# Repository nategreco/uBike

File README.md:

# Universal Bike Controller
The Universal Bike Controller is an open-source project aimed at providing a drop-in replacement for the factory console on NordicTrack® S-series exercise bikes (s10i, s15i, s22i, and s27i). This project allows you to upgrade and customize your bike's control system with new features and improvements.

## Explanation
The factory consoles on NordicTrack® S-series bikes may lack certain features or customization options that users desire. The Universal Bike Controller project addresses these limitations by providing an open-source solution that simplifies the hardware on the bike while unlocking connectivity to other third-party apps (Zwift®, Rouvy®, Peloton®) and smart devices.

(Tablet not included)

## Features
- Drop-in replacement controller for the iFit console
  - **Note - This controller and the OEM console cannot be used together**
- Full incline and resistance control via OEM handlebar pushbuttons
- Wireless connectivity to a variety of third-party applications
- 3.5" TFT touchscreen for reseting elapsed time
- USB Type A fast charger port for charging
- Over-the-air support for future software upgrades

## Installation
The replacement uBike console mounts in the current location of the weight tray and plugs into the same two cables as the factory console. Installation is as simple as follows:
1. Turn off the bike
1. Remove the 4 screws from the underside of the weight tray (save them) and remove the weight tray
1. Place the uBike controller in its place, with the connectors facing away from the rider
1. Use the same 4 screws removed from the weight tray to secure the uBike controller
1. Unplug the 2 cables from the factory console and plug them into the new uBike controller
  * **Please see note below on compatability if you do not have a red and yellow connector**

## Compatibility
The Universal Bike Controller is designed to be compatible with the following NordicTrack® S-series exercise bikes:
- s10i
- s15i
- s22i
- s27i

All of these versions have been tested and are working.  Additionally, since 2021 bikes have stopped shipping with the yellow and red mini-DIN connectors to the console, instead they have cables coming directly out of the console.  **If your bike does not have the red and yellow connectors** you will need to buy the cables below:
* Yellow mini-DIN-6 Connector - PN 411540 ([eBay](https://www.ebay.com/itm/255061719835)/[HydraFitness](https://hydrafitnessparts.com/collections/stationary-bike-wires-and-wire-harness/products/nordictrack-comm-s22i-s15i-s10i-stationary-bike-upper-wire-harness-411540))
* Red mini-DIN-8 Connector - PN 411536 ([eBay](https://www.ebay.com/itm/265237954787)/[HydraFitness](https://hydrafitnessparts.com/collections/stationary-bike-wires-and-wire-harness/products/nordictrack-comm-s22i-s15i-s10i-stationary-bike-extension-wire-harness-411536))

## Additional Reference Photos

## Development
Contributing to the project is encouraged and can be done by testing and reporting issues or software/hardware development.

### Hardware Overview
The hardware is composed of the following components:
* Controller PCB board
* [4D LCD 3.5" Capacitive Touch TFT-LCD](https://4dsystems.com.au/products/4dlcd-35480320-ctp-clb-ips/) 
* Controller enclosure
* Base mount for the enclosure

### Software Tools
* FreeCAD - Housing modeling
* KiCad - PCB Design
* nRF Connect 2.3.0 w/ Visual Studio Code extension - Firmware Development
* Python - Misc development and testing scripts

### Building Firmware
* Open folder `firmware/zephyr-project` in VS Code
* Open nRF Connect extension and press 'Create Build Configuration'
* Select 'ubike_v03' board
* Use defaults and press 'Build Configuration'
* Should produce a binary in `firmware/zephyr-project/build/zephyr/zephyr.hex`

### Flashing
* Open nRF Connect Programmer
* Press 'Add file' and select `firmware/zephyr-project/build/zephyr/zephyr.hex`
* Connect a [nRF52840 DK development board](https://www.nordicsemi.com/Products/Development-hardware/nRF52840-DK) or other SWD/JTAG programmer
* Select the development board as programming device
* Press 'Erase & write'

## Authors
* [@nategreco](https://github.com/nategreco)

## Need Hardware?
[Check out our store on Tindie](https://www.tindie.com/products/grecoengineer/universal-bike-controller/)

**Disclaimer**: This project is not affiliated with or endorsed by ICON Health Fitness, Inc (Nordictrack®) or its parent company. Use this software at your own risk, and be aware that modifying your exercise bike may void any warranties.

---

Contributions, feedback, and bug reports are welcome. Feel free to fork, contribute, or open issues to improve the Universal Bike Controller project!

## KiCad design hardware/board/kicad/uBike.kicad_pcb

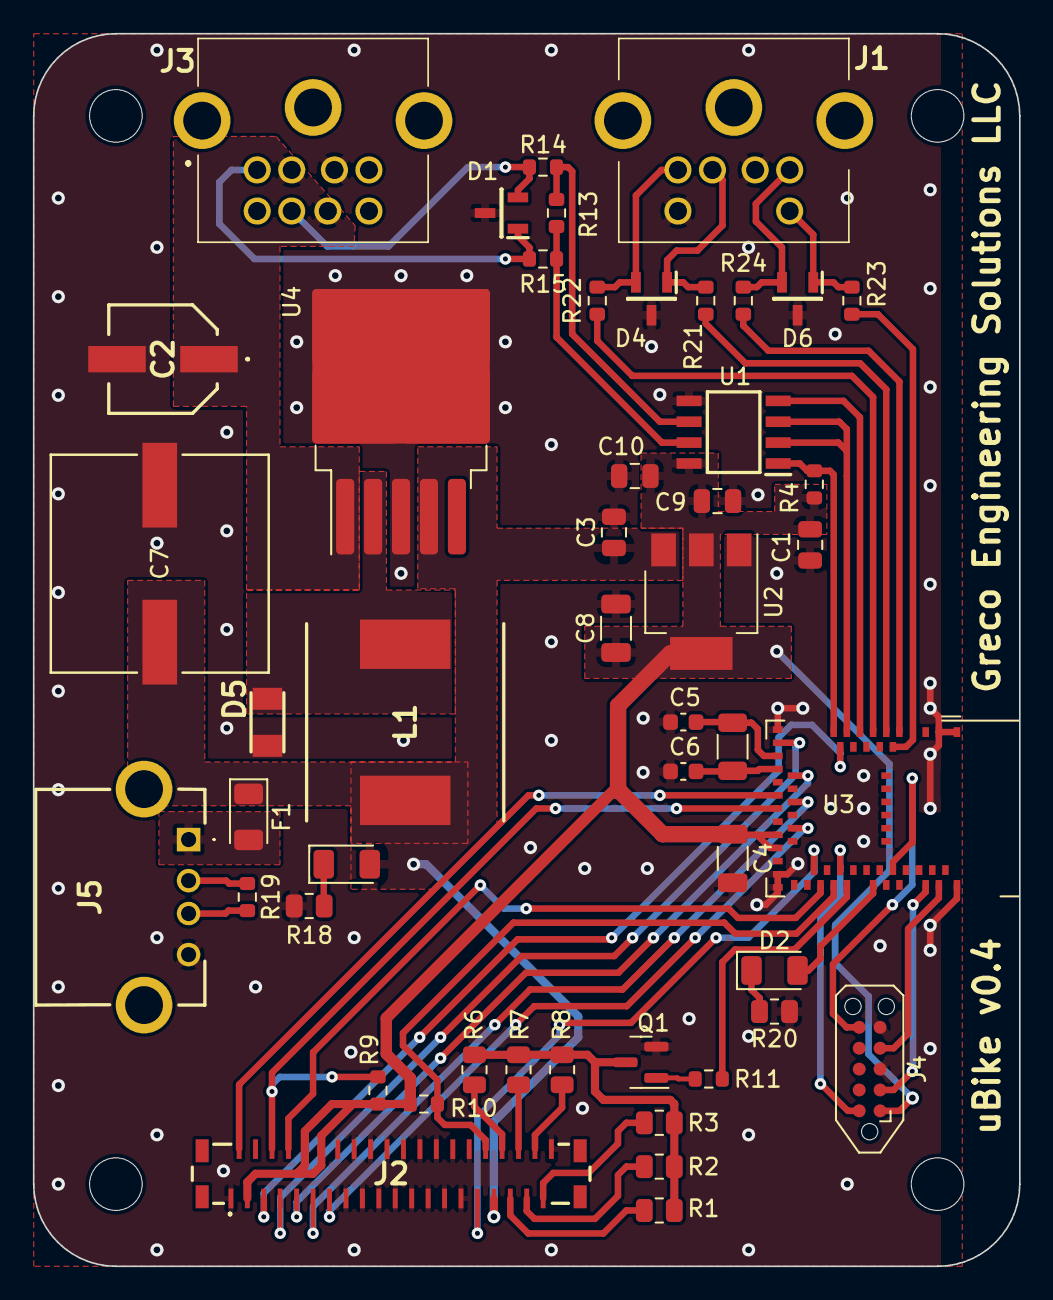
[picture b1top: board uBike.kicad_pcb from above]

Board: 2 copper layers, 60.0 x 75.0 mm, 53 parts (0 on the bottom side), 51 nets.

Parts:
C1, C3, C9: 100n; C_0805_2012Metric
C2: 120u; 16SVF180M
C4, C8: 10u; C_1206_3216Metric
C5, C6: 12p; C_0603_1608Metric
C7: 220u; CHEMI-KE0
C10: 1u; C_0805_2012Metric
D1, D4, D6: CDSOT23-SM712; SOT95P230X117-3N
D2: GREEN; D_1206_3216Metric
D3: RED; D_1206_3216Metric
D5: SS24FL; SODFL3617X108N
F1: 2A; D_1206_3216Metric
H1, H2, H3, H4: MountingHole; MountingHole_3.2mm_M3
J1: KMDGX-6S-BS; KMDGX6SBS
J2: F31S-1A7L1-11040; F31S1A7L111040
J3: KMDGX-8S-BS; KMDGX8SBS
J4: TC2050-IDC-NL; Tag-Connect_TC2050-IDC-NL_2x05_P1.27mm_Vertical
J5: 87520-0010BLF
L1: MSS1210-683MED; INDPM120120X1020N
Q1: MMBT3904; SOT-23
R1, R2, R3, R6, R7, R8, R20: 68; R_0805_2012Metric
R4: 10k; R_0603_1608Metric
R9, R10: 1k69; R_0603_1608Metric
R11: 1k; R_0603_1608Metric
R13: 250; R_0603_1608Metric
R14, R15, R21, R22, R23, R24: 10; R_0603_1608Metric
R18: 330; R_0805_2012Metric
R19: 150; R_0603_1608Metric
U1: SN65HVD08DR; SOIC127P600X175-8N
U2: LD1117S33TR_SOT223; SOT-223-3_TabPin2
U3: MDBT50Q-P1MV2; Raytac_MDBT50Q
U4: LM2596S-5; TO-263-5_TabPin3
X1: 32.768kHz; R_1206_3216Metric

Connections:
+3.3V: C1.1, C4.1, C8.1, C9.2, C10.2, J2.3, J2.10, J2.12, J4.1, R4.1, R9.1, R10.1, U1.8 (VCC), U2.2 (VO), U3.28 (VDD), U3.30 (VDDH)
+5V: C3.1, C7.1, D3.2 (A), F1.1, J2.33, L1.2, U2.3 (VI), U4.4 (FB)
+12V: C2.1 (+), J3.1, J3.7, U4.1 (VIN)
BL_DRAIN: Q1.3 (C), R1.1, R2.1, R3.1, R6.2, R7.2, R8.2
BL_PWM: R11.1, U3.41 (P0.17)
CS: J2.9, U3.19 (P0.26)
CTP_SCL: J2.6, R9.2, U3.24 (P0.08)
CTP_SDA: J2.32, R10.2, U3.39 (P0.15)
DE: U1.2 (~RE), U1.3 (DE), U3.12 (P0.31/AIN7)
GND: C1.2, C2.2 (-), C3.2, C4.2, C5.2, C6.2, C7.2, C8.2, C9.1, C10.1, D1.3, D4.3, D5.2 (A), D6.3, J1.2, J1.6, J2.1, J2.14, J2.15, J2.16, J2.17, J2.18, J2.19, J2.20, J2.21, J2.22, J2.23, J2.24, J2.25, J2.26, J2.27, J2.28, J2.29, J2.30, J2.40, J3.2, J3.6, J4.3, J4.5, J5.4, Q1.2 (E), R18.1, R20.1, U1.5 (GND), U2.1 (GND), U3.1 (GND), U3.2 (GND), U3.15 (GND), U3.32 (VBUS), U3.33 (GND), U3.55 (GND), U4.3 (GND)
IN1: R21.1, U3.6 (P1.13)
IN2: R22.2, U3.8 (P1.15)
IN3: R24.2, U3.4 (P1.11)
IN4: R23.1, U3.5 (P1.12)
unnamed: D2.2 (A), U3.44 (P0.20)
unnamed: D2.1 (K), R20.2
unnamed: D3.1 (K), R18.2
unnamed: D4.1, J1.1, R21.2
unnamed: D4.2, J1.3, R22.1
unnamed: D5.1 (K), L1.1, U4.2 (OUT)
unnamed: D6.1, J1.8, R23.2
unnamed: D6.2, J1.5, R24.1
unnamed: F1.2, J5.1
unnamed: J2.34, R6.1
unnamed: J2.35, R1.2
unnamed: J2.36, R7.1
unnamed: J2.37, R2.2
unnamed: J2.38, R8.1
unnamed: J2.39, R3.2
unnamed: J5.2, R19.1
unnamed: J5.3, R19.2
unnamed: Q1.1 (B), R11.2
unnamed: R13.2, R14.2, U1.6 (A)
unnamed: R13.1, R15.2, U1.7 (B)
unnamed: C5.1, U3.17 (XL1/P0.00), X1.2
unnamed: C6.1, U3.18 (XL2/P0.01), X1.1
RESET: J2.7, U3.16 (P0.27)
RS: J2.8, U3.37 (P0.13)
RS485_A: D1.2, J3.4, R14.1
RS485_B: D1.1, J3.3, R15.1
RX: R4.2, U1.1 (R), U3.14 (P0.30/AIN6)
SCL: J2.11, U3.23 (TRACECLK/P0.07)
SDI: J2.2, U3.22 (P0.06)
SDO: J2.13, U3.27 (TRACEDATA2/P0.11)
SWCLK: J4.4, U3.53 (SWDCLK)
SWDIO: J4.2, U3.51 (SWDIO)
SWD_RST: J4.10, U3.40 (~RESET/P0.18)
SWO: J4.6, U3.47 (TRACEDATA0/P1.00)
TX: U1.4 (D), U3.10 (P0.29/AIN5)
YD: J2.5, U3.13 (P0.28/AIN4)
YU: J2.31, U3.36 (P0.14)

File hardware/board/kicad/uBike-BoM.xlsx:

|  |  | uBike v0.4 Bill of Materials
Item # | *Designator | *Qty | Manufacturer | *Mfg Part # | Description / Value | *Package/Footprint | Type | Your Instructions / Notes
1.0 | C1, C3, C9 | 3.0 | AVX | 08053C104KAT2A | 100nF - Unpolarized capacitor, 25V, 10% | 0805_2012Metric
2.0 | C2 | 1.0 | Panasonic | 20SVPF120M | 120uF - Organic Polymer Capacitors 20V, ESR 25mohm | 20SVPF120M
3.0 | C4, C8 | 2.0 | Murata Electronics | GRM319R61E106MA12D | 10uF - Unpolarized capacitor, 25V, 10% | 1206_3216Metric
4.0 | C5, C6 | 2.0 | Kemet | C0603C120F5GACTU | 12pF - Unpolarized capacitor, 50V, 1% | 0603_1608Metric
5.0 | C7 | 1.0 | Chemi-Con | EMVY630ARA221MKE0S | 220uF - Electrolytic Capacitor, 63 Volt | EMVY630ARA221MKE0S
6.0 | C10 | 1.0 | Murata Electronics | GRT21BR61E105KE13L | 1uF - Unpolarized capacitor, 25V, 10% | 0805_2012Metric
7.0 | D1, D4, D6 | 3.0 | Bourns | CDSOT23-SM712 | Surface Mount Bi-directional TVS Diode | SOT-23
8.0 | D2 | 1.0 | Lite-On | LTST-C150KGKT | Light emitting diode (Green) | 1206_3216Metric
9.0 | D3 | 1.0 | Lite-On | LTST-C150KRKT | Light emitting diode (Red) | 1206_3216Metric
10.0 | D5 | 1.0 | Onsemi | SS24FL | Schottky Diodes & Rectifiers 40V, 2A SCHOTTKY | SS24FL
11.0 | F1 | 1.0 | Littelfuse, Inc | 1206L200SLYR | 2A Resettable Fuse | 1206_3216Metric
12.0 | H1, H2, H3, H4 | 4.0 | - | - | Mounting Hole without connection | - |  | DO NOT POPULATE
13.0 | J1 | 1.0 | Kycon, Inc. | KMDGX-6S-BS | 6P mini-DIN connector female (socket) | KMDGX6SBS
14.0 | J2 | 1.0 | Amphenol ICC | F31S-1A7L1-11040 | 40P FPC connector | F31S1A7L111040
15.0 | J3 | 1.0 | Kycon, Inc. | KMDGX-8S-BS | 8P mini-DIN connector female (socket) | KMDGX8SBS
16.0 | J4 | 1.0 | - | - | 10P Tag Connect footprint (DNP) | - |  | DO NOT POPULATE
17.0 | J5 | 1.0 | Amphenol ICC | 87520-0010BLF | USB Type A, Standard, Right Angle, Through Hole | 875200010BLF
18.0 | L1 | 1.0 | Coilcraft | MSS1210-683MED | Power Inductors 68uH Shld 20% 4.3A 84mOhms | MSS1210-683MED
19.0 | Q1 | 1.0 | Diotec Semiconductor | MMBT3904 | Bipolar NPN Transistor | SOT-23
20.0 | R1, R2, R3, R6, R7, R8, R20 | 7.0 | Panasonic | ERJ-P06F68R0V | Thick Film Resistor – 68 (1/2W) | 0805_2012Metric
21.0 | R4 | 1.0 | Panasonic | ERJ-PA3F1002V | Thick Film Resistor – 10k (1/4W) | 0603_1608Metric
22.0 | R9, R10 | 2.0 | Panasonic | ERJ-PA3F1691V | Thick Film Resistor – 1.69k (1/4W) | 0603_1608Metric
23.0 | R11 | 1.0 | Panasonic | ERJ-PA3F1001V | Thick Film Resistor – 1k (1/4W) | 0603_1608Metric
24.0 | R13 | 1.0 | Panasonic | ERJ-PA3F2200V | Thick Film Resistor – 220 (1/4W) | 0603_1608Metric
25.0 | R14, R15, R21, R22, R23, R24 | 6.0 | Panasonic | ERJ-PA3F10R0V | Thick Film Resistor – 10 (1/4W) | 0603_1608Metric
26.0 | R18 | 1.0 | Panasonic | ERJ-PA3F3300V | Thick Film Resistor – 330 (1/2W) | 0805_2012Metric
27.0 | R19 | 1.0 | Panasonic | ERJ-PA3F1500V | Thick Film Resistor – 150 (1/4W) | 0603_1608Metric
28.0 | U1 | 1.0 | Texas Instruments | SN65HVD08DR | Wide Supply Range RS-485 Transceiver | SOIC127P600X175-8N
29.0 | U2 | 1.0 | STMicroelectronics | LD1117S33TR | 3.3v Fixed Low Drop Positive Voltage Regulator | SOT-223-3
30.0 | U3 | 1.0 | Raytac Corporation | MDBT50Q-1MV2 | Nordic nRF52840 SoC Solution | MDBT50Q
31.0 | U4 | 1.0 | Texas Instruments | LM2596SX-5.0/NOPB | Switching Voltage Regulators 150 KHZ 3A Buck | TO-263-5
32.0 | X1 | 1.0 | NDK | NX3215SA-32.768K-STD-MUA-9 | Crystal oscillator - 32.768 kHz | 1206.0
Need a quick and accurante quote? Need an efficient production? Please read SMT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
Click for Instructions on How to Create a BOM

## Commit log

2023-09-25 Initial commit
    Initial starting point w/ v0.3 hardware files, current firmware project,
    and GPL v3 license.
2023-11-07 Several changes, including FTMS semaphore
    - Added semaphore to FTMS to guarantee notify after write
    - Added early returns to all notifications when not connected
    - Added clang-format file
2023-11-19 Reversed to using kscan callback to reset the screen
2023-11-20 Revert "Reversed to using kscan callback to reset the screen"
    This reverts commit 9253e350cdc0548603a149c64ceb450167267d3a.
2023-11-21 Added a 7-digit SHA on the screen, reverted kscan revert
2023-11-21 Implemented DFU
2023-11-23 Compiles but doesn't run
2023-11-24 removed warnings but still fails to boot
2023-11-25 Builds and boots
2023-11-25 Turned off logging to shrink size - Now DFU works but unstable
2023-11-26 Made params static for uuid indicate
2023-11-26 Switched to notify instead of indicate for control point
2023-11-26 Added troubleshooting lines
2023-11-27 Testing DFU commit
2023-12-03 Disabled encryption on the control point
2023-12-03 Reverted troubleshooting lines
2023-12-03 Improved FTMS stability
2023-12-04 Got rid of some build warnings
2023-12-15 Got nRF52840dk building w/o mcuboot mgr
2023-12-16 nRF5340 builds
2023-12-20 Switched to NRF timer
2023-12-28 Roughed in
2023-12-30 Changed to 2-layer board
2023-12-30 Rounded edges, some cleanup to reduce warnings
2023-12-30 Added stitching vias, other fixes
2023-12-31 Schematic cleanup
2023-12-31 Finalized for review
2024-01-02 Changed 2.2uF cap footprints and a bit more cleanup
2024-01-03 Created v0.4 board from v0.3 files
2024-01-03 Enabled pull-up resistor and removed lcd reset
2024-01-03 Added inline resistors for ESD on inputs, created order T-V26W325984A
2024-01-07 First attempt at v4 enclosure
2024-01-31 First pass working
2024-02-03 Moved up pcb 1.5mm
2024-02-03 Changed tilt to 20 degrees
2024-02-03 Closed up USB hole
2024-02-04 Accidently checked-in backup
2024-02-11 First pass at LM2596 regulator
2024-02-11 Some general cleanup
2024-02-12 Updated BOM
2024-11-13 Updated model
2024-11-14 Added missing screw holes
2024-11-25 Added version tag to display
